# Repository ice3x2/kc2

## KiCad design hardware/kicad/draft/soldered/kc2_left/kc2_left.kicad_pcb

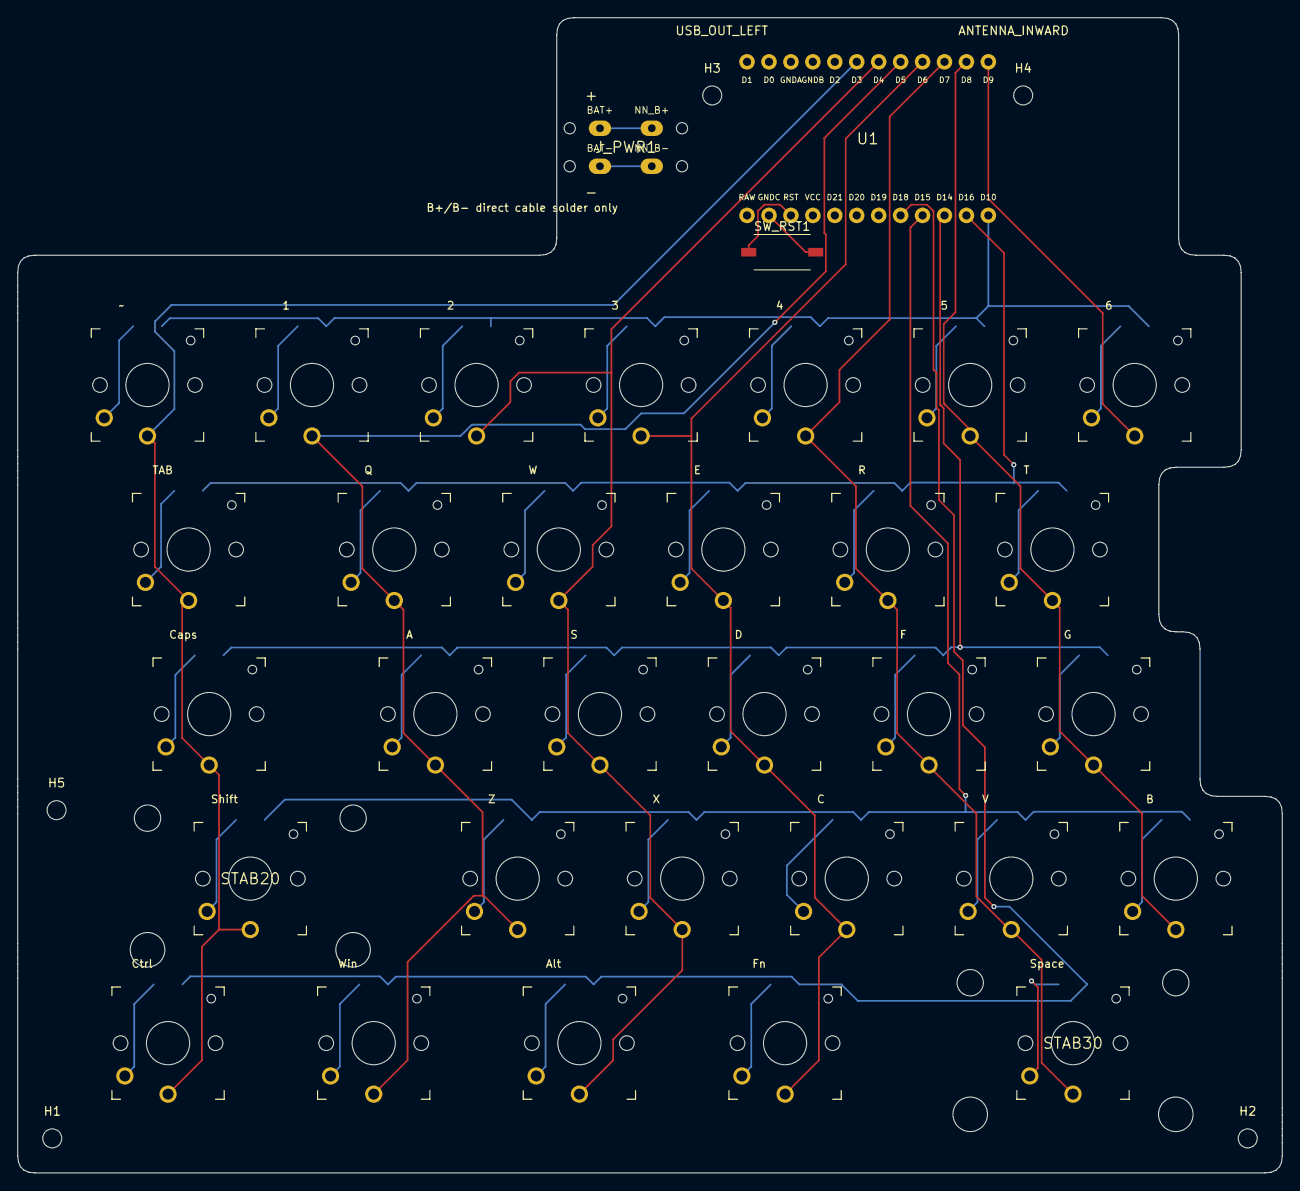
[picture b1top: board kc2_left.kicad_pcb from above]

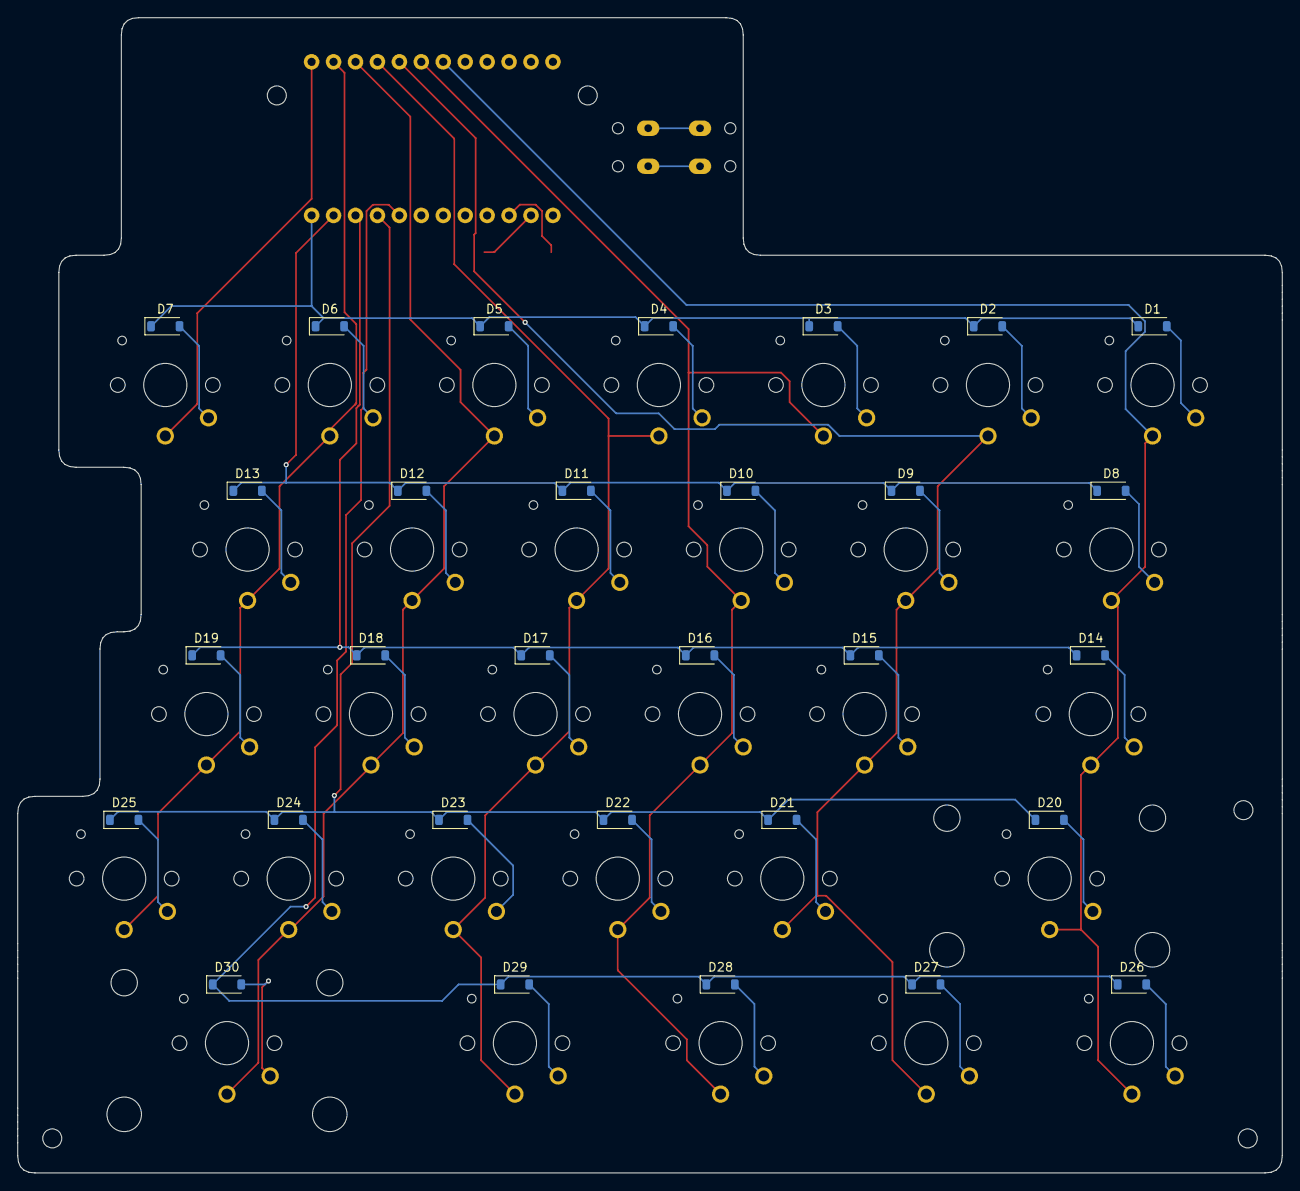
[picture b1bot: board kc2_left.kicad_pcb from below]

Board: 2 copper layers, 146.4 x 133.8 mm, 70 parts (30 on the bottom side), 46 nets.

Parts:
D1, D2, D3, D4, D5, D6, D7, D8, D9, D10, D11, D12, D13, D14, D15, D16, D17, D18, D19, D20, D21, D22, D23, D24, D25, D26, D27, D28, D29, D30: 1N4148W_SOD-123; D_SOD-123
H1, H2, H3, H4, H5: M2_NPTH_2.2; MountingHole_2.2mm_M2
J_PWR1: BAT_NN_direct_solder; DirectSolderPowerPads
STAB20, STAB30: PCB_mount_stab_for_2.25u; PCB_Mount_2u_Stabilizer_NPTH
SW1: KEY_01; SW_Kailh_Choc_V1V2_THT_Hybrid
SW2: KEY_02; SW_Kailh_Choc_V1V2_THT_Hybrid
SW3: KEY_03; SW_Kailh_Choc_V1V2_THT_Hybrid
SW4: KEY_04; SW_Kailh_Choc_V1V2_THT_Hybrid
SW5: KEY_05; SW_Kailh_Choc_V1V2_THT_Hybrid
SW6: KEY_06; SW_Kailh_Choc_V1V2_THT_Hybrid
SW7: KEY_07; SW_Kailh_Choc_V1V2_THT_Hybrid
SW8: KEY_08; SW_Kailh_Choc_V1V2_THT_Hybrid
SW9: KEY_09; SW_Kailh_Choc_V1V2_THT_Hybrid
SW10: KEY_10; SW_Kailh_Choc_V1V2_THT_Hybrid
SW11: KEY_11; SW_Kailh_Choc_V1V2_THT_Hybrid
SW12: KEY_12; SW_Kailh_Choc_V1V2_THT_Hybrid
SW13: KEY_13; SW_Kailh_Choc_V1V2_THT_Hybrid
SW14: KEY_14; SW_Kailh_Choc_V1V2_THT_Hybrid
SW15: KEY_15; SW_Kailh_Choc_V1V2_THT_Hybrid
SW16: KEY_16; SW_Kailh_Choc_V1V2_THT_Hybrid
SW17: KEY_17; SW_Kailh_Choc_V1V2_THT_Hybrid
SW18: KEY_18; SW_Kailh_Choc_V1V2_THT_Hybrid
SW19: KEY_19; SW_Kailh_Choc_V1V2_THT_Hybrid
SW20: KEY_20; SW_Kailh_Choc_V1V2_THT_Hybrid
SW21: KEY_21; SW_Kailh_Choc_V1V2_THT_Hybrid
SW22: KEY_22; SW_Kailh_Choc_V1V2_THT_Hybrid
SW23: KEY_23; SW_Kailh_Choc_V1V2_THT_Hybrid
SW24: KEY_24; SW_Kailh_Choc_V1V2_THT_Hybrid
SW25: KEY_25; SW_Kailh_Choc_V1V2_THT_Hybrid
SW26: KEY_26; SW_Kailh_Choc_V1V2_THT_Hybrid
SW27: KEY_27; SW_Kailh_Choc_V1V2_THT_Hybrid
SW28: KEY_28; SW_Kailh_Choc_V1V2_THT_Hybrid
SW29: KEY_29; SW_Kailh_Choc_V1V2_THT_Hybrid
SW30: KEY_30; SW_Kailh_Choc_V1V2_THT_Hybrid
SW_RST1: NW3-A06-B3 RST; SW_NW3_A06_B3_SMD
U1: nice!nano_v2_socket_24pin; NiceNanoV2_Socket_24Pin

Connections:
BAT+: J_PWR1.BAT+, J_PWR1.NN_B+
BAT-: J_PWR1.BAT-, J_PWR1.NN_B-
GND: SW_RST1.2, U1.GND_C
LK01_D: D1.2, SW1.2
LK02_D: D2.2, SW2.2
LK03_D: D3.2, SW3.2
LK04_D: D4.2, SW4.2
LK05_D: D5.2, SW5.2
LK06_D: D6.2, SW6.2
LK07_D: D7.2, SW7.2
LK08_D: D8.2, SW8.2
LK09_D: D9.2, SW9.2
LK10_D: D10.2, SW10.2
LK11_D: D11.2, SW11.2
LK12_D: D12.2, SW12.2
LK13_D: D13.2, SW13.2
LK14_D: D14.2, SW14.2
LK15_D: D15.2, SW15.2
LK16_D: D16.2, SW16.2
LK17_D: D17.2, SW17.2
LK18_D: D18.2, SW18.2
LK19_D: D19.2, SW19.2
LK20_D: D20.2, SW20.2
LK21_D: D21.2, SW21.2
LK22_D: D22.2, SW22.2
LK23_D: D23.2, SW23.2
LK24_D: D24.2, SW24.2
LK25_D: D25.2, SW25.2
LK26_D: D26.2, SW26.2
LK27_D: D27.2, SW27.2
LK28_D: D28.2, SW28.2
LK29_D: D29.2, SW29.2
LK30_D: D30.2, SW30.2
L_COL0: SW1.1, SW8.1, SW14.1, SW20.1, SW26.1, U1.D3
L_COL1: SW2.1, SW9.1, SW15.1, SW21.1, SW27.1, U1.D5
L_COL2: SW3.1, SW10.1, SW16.1, SW22.1, SW28.1, U1.D4
L_COL3: SW4.1, SW11.1, SW17.1, SW23.1, SW29.1, U1.D6
L_COL4: SW5.1, SW12.1, SW18.1, SW24.1, SW30.1, U1.D7
L_COL5: SW6.1, SW13.1, SW19.1, SW25.1, U1.D8
L_COL6: SW7.1, U1.D9
L_ROW0: D1.1, D2.1, D3.1, D4.1, D5.1, D6.1, D7.1, U1.D10
L_ROW1: D8.1, D9.1, D10.1, D11.1, D12.1, D13.1, U1.D16
L_ROW2: D14.1, D15.1, D16.1, D17.1, D18.1, D19.1, U1.D14
L_ROW3: D20.1, D21.1, D22.1, D23.1, D24.1, D25.1, U1.D15
L_ROW4: D26.1, D27.1, D28.1, D29.1, D30.1, U1.D18
RST: SW_RST1.1, U1.RST
